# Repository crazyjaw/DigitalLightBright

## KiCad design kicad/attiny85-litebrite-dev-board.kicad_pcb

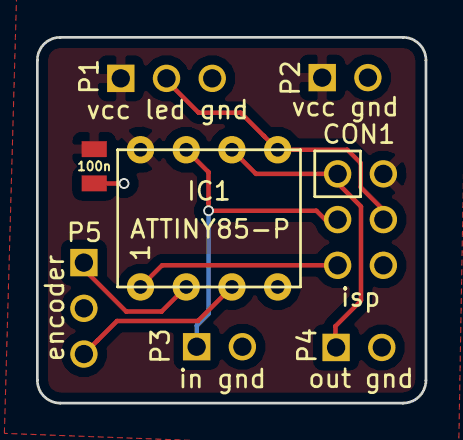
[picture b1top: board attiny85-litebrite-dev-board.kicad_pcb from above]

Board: 2 copper layers, 21.6 x 20.3 mm, 8 parts (0 on the bottom side), 8 nets.

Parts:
C1: 100n; C0805_nosilkscreen
CON1: isp; pin_array_2x3_100mil_pth
IC1: ATTINY85-P; dip8
P1: vcc led gnd; header_01x03_40mil_60mil
P2: vcc gnd; header_01x02_40mil_60mil
P3: in gnd; header_01x02_40mil_60mil
P4: out gnd; header_01x02_40mil_60mil
P5: encoder; header_01x03_40mil_60mil

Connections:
//reset: CON1.5, IC1.1
/gnd: C1.2, CON1.6, IC1.4, P1.3, P2.2, P3.2, P4.2, P5.2
/miso: CON1.1, IC1.6, P4.1
/mosi: CON1.4, IC1.5, P1.2
/pb3: IC1.2, P5.1
/pb4: IC1.3, P5.3
/sck: CON1.3, IC1.7, P3.1
/vcc: C1.1, CON1.2, IC1.8, P1.1, P2.1

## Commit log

2016-04-19 initial cad commit
2016-04-19 added arduino source
2016-04-19 added pbc gerber files
2016-04-19 added cap to PBC, updated board labling
2016-06-14 dev board, using dip8 attiny85
2016-06-16 buffed lense. added mounting shims

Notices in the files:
kicad/attiny85-litebrite-dev-board.kicad_pcb:
(c) 2016
